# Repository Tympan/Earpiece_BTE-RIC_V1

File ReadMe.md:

# Tympan Behind The Ear Units

This repo contains hardware designs for Tympan compatible BTE units.

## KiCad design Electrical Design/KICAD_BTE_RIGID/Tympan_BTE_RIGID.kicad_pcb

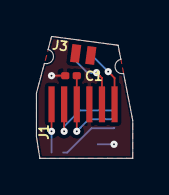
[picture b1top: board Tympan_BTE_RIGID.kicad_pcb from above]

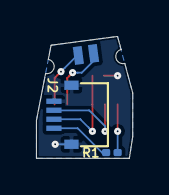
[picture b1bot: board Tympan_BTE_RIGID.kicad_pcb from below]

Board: 2 copper layers, 5.3 x 6.8 mm, 5 parts (2 on the bottom side), 7 nets.

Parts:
C1: 220nF; C_0201_0603Metric
J1: Input Wire Connector; BTE_INPUT
J2: FPC Connector; 10062827-0410EDHLF
J3: CS44 Connector; CS44
R1: 50R; R_0201_0603Metric

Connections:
+3V3: C1.1, J1.3, J2.3
/CLK: J1.2, J2.2
/DATA: J1.1, R1.1
/SPK+: J1.6, J3.3
/SPK-: J1.5, J3.4
GND: C1.2, J1.4, J2.1, J2.5, J2.6
unnamed: J2.4, R1.2

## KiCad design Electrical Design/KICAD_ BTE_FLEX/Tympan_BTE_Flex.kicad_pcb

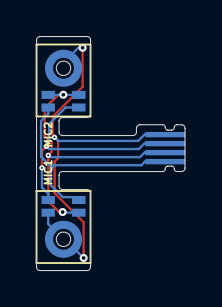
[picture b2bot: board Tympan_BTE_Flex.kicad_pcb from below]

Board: 2 copper layers, 8.2 x 13.0 mm, 3 parts (3 on the bottom side), 4 nets.

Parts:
FPC1: FPC_MALE; 10062827-0410EDHLF FPC Flex
MIC1, MIC2: IM69D130

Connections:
/CLK: FPC1.3, MIC1.3, MIC2.3
/DATA: FPC1.1, MIC1.1, MIC2.1
GND: FPC1.4, MIC1.4, MIC1.5, MIC2.5
VDD: FPC1.2, MIC1.2, MIC2.2, MIC2.4

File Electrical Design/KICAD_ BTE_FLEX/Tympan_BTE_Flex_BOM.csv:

Reference, Quantity, Value, Footprint,Manufacturer,Part Number
MIC1 MIC2 ,2,IM69D130,Tympan_BTE_Flex:IM69D130,Infineon,IM69D130V01XTSA1

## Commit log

2019-07-11 Initial Release for Review of Mechanical Design
2019-07-16 Corrected faulty faces including a knife edge near the lip.
    Other Solidworks design files have not yet been updated, as they will be corrected soon.
2019-07-16 Changed FPC connector, which affected many parts.
2019-07-24 Fixed hanging chad on Right Enclosure
2019-09-18 Adding Kicad Circuit Design for Flex PCB
2019-09-18 Adding design files for the flexi board
2019-09-18 Updated dates and version
2019-09-19 Changed name of gerber file for clarity
2019-09-19 Added Rigid PCB design
    There are two PCB layouts. One is an array of 5 boards, the other is just one
2019-09-19 Update gitignore
2019-09-19 deleted the zip files
2019-09-20 Updated SW pad locations and Wiring Overview to match actual PCB layout
    Updated pad locations in SW
    Updated wiring overview for rigid PCB to match actual PCB layout
2019-09-20 Labeled wire colors and swapped the +- speaker connections
2019-11-01 Corrected wiring diagram
    Corrected wiring diagram based on revisions to the earpiece shield, in which the USB mini pinout changed.
2020-09-10 changed file extensions from upper case to lower case
    This will work for the solidworks zipped folder, but maybe not the others?
2020-09-10 Changed file extensions to lower case
2020-09-10 Renaming with lowercase extensions
2020-09-16 added specifications to the PCB schematics and made pdf of schem
2021-02-23 added initial ReadMe
2021-03-04 Updated strain relief and added BOM for earpiece
    Updated strain relief and added BOM for earpiece
2021-03-08 Upload Mic gasket without slots
2021-06-08 Added Render with callout to components
2021-06-08 Adding render of earpiece
2021-06-15 Added datasheets for earpiece components
2021-06-15 Adding Photos of the Earpieces
2021-06-15 Adding earpiece renders
2021-06-15 Adding section view of mic ports
2021-09-28 Corrected CLK and DATA pinout to account for changes to Earpiece Shield
2022-07-11 Firmware for testing earpieces.
2022-07-13 Fixed issue where both mics needed to be plugged in at once. Now only the left PDM mic is used.
2022-07-13 Small cleanup of code
2022-07-13 Added comments to clarify right and left earpieces
2022-09-21 Updated SW Pack and Go zip file for Earpice CAD
2022-10-19 Adding a floder for test firmware
    first example of BTE production test firmware
2022-11-16 Started Building Assembly Guide
    The CS-44 placement is critical to all of the parts fitting. It is, basically, the keystone of the entire build.
